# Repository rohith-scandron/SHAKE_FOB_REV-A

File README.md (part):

# SHAKE_FOB_REV-A

A PCB keychain: a shake-activated OLED "digital pet" fob. Sleeps at ~0 µA-class draw
until shaken, wakes and shows an emoji/gif on a small I2C OLED, advances to the next
one on a gentle shake, and sleeps again after 10 s idle. BLE included for a future
companion app to push new gifs. Charges and programs over USB-C. Built for JLCPCB
fab + assembly, optimized for the smallest board that still fits the parts.

## Key specs

| | |
|---|---|
| MCU | ESP32-C3FH4 (bare QFN32, 4 MB integrated flash, RISC-V, BLE 5) |
| Accelerometer | MMA8452QR1 (QFN-16 3×3 mm), transient (high-pass) wake interrupt, no polling needed. Replaced LIS2DH12TR, which is JLC "Standard PCBA only" |
| Charger | MCP73831T-2ACI/OT (SOT23-5), USB-C VBUS in, 147 mA charge rate (R_PROG = 6.8 kΩ) |
| 3V3 rail | XC6206P332MR (SOT23-3), ~1 µA Iq, 200 mA — sized for sleep-dominated duty |
| USB-C | TYPE-C-31-M-12, 16-pin, native USB D+/D− straight to the MCU (no CP2102/CH340) |
| Display | **off-board** — 0.96" 128×64 I2C OLED (SSD1306), 4 bare solder pads (GND/VCC/SCL/SDA), swappable |
| Battery | **off-board** — single-cell LiPo via 2 bare solder pads, user-sourced (the seller's cells come as bare leads, not a pre-terminated JST plug) |
| Buttons | RESET (EN→GND) and BOOT (GPIO9→GND), small SMD tactile — SuperMini-style |
| Board | 2-layer, target ≈ 25–30 × 18–22 mm, JLCPCB fab + SMT assembly |

All ICs above are on the JLCPCB parts library (LCSC part numbers in the BOM notes
below); the display and battery are intentionally *not* SMT parts — they connect
through headers/wires so either can be swapped without touching the PCB.

## BOM / JLCPCB parts library status

Checked against LCSC/JLCPCB directly (not from memory). Prices/stock are a snapshot
— reverify before ordering.

| Ref | Part | LCSC | JLCPCB library | Notes |
|---|---|---|---|---|
| U1 | ESP32-C3FH4, QFN-32-EP (5×5 mm) | C2858491 | Extended | 4233 in stock at check time |
| U4 | MMA8452QR1, QFN-16 (3×3 mm) | C11360 | Extended | Economic-PCBA OK, MSL1, 2,916 in stock. Replaced LIS2DH12TR (C110926: LGA, X-ray required → Standard PCBA only) |
| U3 | MCP73831T-2ACI/OT, SOT23-5 | C424093 | Extended (assumed) | not confirmed live, low risk either way |
| U4 | XC6206P332MR, SOT23-3 | C5446 | **Basic** | ~$0.02, ~1 µA Iq |
| U5 | USBLC6-2SC6, SOT23-6 | C7519 | Extended | USB ESD protection, use the genuine ST part |
| D2 | 1N4148WS, SOD-323 | C2128 | **Basic** | VBUS→SYS. Silicon, not Schottky, for nA reverse leakage on battery (see Power architecture) |
| Q1 | AO3401A P-MOSFET, SOT-23 | C15127 | **Basic** | BAT→SYS load-share switch (Microchip AN1149), ~14 mV drop vs ~0.3 V for a Schottky |
| R15, R16 | 1 MΩ 0402 battery-sense divider → GPIO3 | C26083 | **Basic** | + C19 100 nF; 2.1 µA |
| J1 | TYPE-C-31-M-12, USB-C 16-pin | C165948 | Extended | USB 2.0 subset only (VBUS/GND/D±/CC/SBU) |
| Y1 | 40 MHz crystal, 3225, C_L = 12 pF | **C5380316** (SOSET) | — | imported and confirmed 40 MHz on import; C13738 was mis-picked earlier (turned out to be 16 MHz) and has been removed |
| SW1, SW2 | TS342A2P tactile switch, 4×3×2 mm | C398055 | Extended | RESET + BOOT; checked for a Basic alternative, none found |
| TP1–TP4 | 4× bare solder pad (KiCad `TestPoint` lib) — OLED: GND/VCC/SCL/SDA | generic | n/a, not a real component | replaces a 2.54mm header — no connector to import, no BOM/CPL line |
| TP5–TP6 | 2× bare solder pad (KiCad `TestPoint` lib) — battery: BAT+/GND | generic | n/a, not a real component | replaces the JST-PH connector (below) — the actual battery source is bare leads, not a pre-terminated plug, so there's nothing to keep a connector for |
| ~~J3~~ | ~~S2B-PH-SM4-TB, SMD JST-PH 2-pin~~ | ~~C295747~~ | ~~Extended~~ | **dropped** — imported into the library, then superseded by TP5/TP6 once it turned out the battery isn't sold pre-terminated |
| ANT | Johanson 2450AT18A100E chip antenna | C89334 | — | in stock at check time; decided over a PCB trace, see Antenna below |
| — | RF matching, **chip-side only** (2×C 1.2–1.8pF + 1×L 2.0–3.0nH, 0201, pi network) | generic 0201 | Basic-class, commodity | antenna-side network deliberately dropped for a minimal BOM — see MCU wiring below |
| — | passives (0402/0603/0201 R/C) | generic | Basic-class, commodity | |

**11 Extended parts** after the two free swaps below (JLC BOM check,
2026-09-23): ESP32-C3FH4, MMA8452QR1, MCP73831, USBLC6-2SC6, TS342A2P,
USB-C (C165948), 40MHz crystal (C5380316), antenna (C89334), 1.5pF RF caps
(C1552), 2.2nH (C27122), 0402 LED (C71911). At $3 each that's ≈ **$33** in
loading fees. An earlier count of "5" was wrong. Free swaps with the same
footprint: 10k C25531 → **C25744** (R7–R9, R13, R14) and 100k C25530 →
**C25741** (R10), both Basic. Nothing else on the list has a Basic
equivalent in the same footprint.

**Assembly tier: Economic PCBA.** LIS2DH12TR (and its SC7A20 clone) is
flagged "Standard only" by JLC (LGA → X-ray, MSL3), so the accelerometer was
swapped to MMA8452QR1 (QFN, MSL1, Economic OK). It costs ~$1 more per part and
+3µA of sleep current, but saves ~$17 in Standard setup and the forced edge
rails.

## MCU wiring — verified against Espressif's datasheet + hardware design guidelines

Pulled `esp32-c3_datasheet_en.pdf` and the ESP32-C3 hardware design guidelines
directly (saved in [`datasheets/`](datasheets/)) rather than relying on memory.
Key points that affect the schematic:

- **Power pins**, each needs local decoupling: VDD3P3 (analog/RF, pins 2–3) — 10 µF
  + 0.1 µF (Espressif also suggests an LC filter inductor here for harmonic
  suppression — **dropped**, it's RF-certification margin rather than something
  needed for function, and the linear LDO feeding this rail is already low-noise);
  VDD3P3_RTC (pin 11) — 0.1 µF; VDD3P3_CPU (pin 17) — 0.1 µF; **VDD_SPI (pin 18)** —
  tie directly to 3V3 with a 1 µF cap, since the in-package flash on the FH4 needs
  VDD_SPI ≥ 3.0 V and this pin *cannot* be used as a GPIO on this variant. Add an ESD
  diode + ≥10 µF at the board's main power entrance too.
- **CHIP_EN**: must never float. Standard R=10 kΩ / C=1 µF RC delay to 3V3, RESET
  button pulls it to GND. Espressif's own note: on a slow/battery power rise, RC
  alone can be marginal — accepted as-is here (nearly every hobby ESP32 board ships
  with just RC), flagged as a known limitation rather than adding a supervisor IC.
- **Strapping pins** (GPIO2, GPIO8, GPIO9): GPIO9 gets an explicit pull-up
  (10 kΩ→3V3) *and* the datasheet explicitly warns not to put a capacitor on it, or
  the chip can drop into download mode — matters because BOOT button lands here.
  GPIO2 also gets a 10 kΩ pull-up ("recommended... due to glitches" even though it
  doesn't strictly gate boot mode). GPIO8 gets a 10 kΩ pull-up (R14): download boot needs GPIO8 = 1 (Table 3-3).
- **Crystal**: 40 MHz is compulsory (no internal option), ±10 ppm. Standard 2-pad
  crystal + 2 load caps. Espressif also suggests a 24 nH series inductor on the
  XTAL_P trace for harmonic suppression — **dropped**, same reasoning as the
  VDD3P3 filter above: their own guideline calls the value an "initial
  suggestion... adjust after an overall test," i.e. margin, not a requirement.
  ≥2 mm gap from the chip's clock pin, no vias on the clock trace itself, keep
  it away from the RF trace.
  **Load cap value, corrected:** the formula is `C_L = (C1×C2)/(C1+C2) + C_stray`
  (checked directly against Espressif's live HTML page — the PDF's text extraction
  had jumbled the fraction and put C_stray inside the denominator, which gave a
  wrong answer the first time around). With C1=C2=C, C_stray≈3 pF (typical PCB
  estimate), and our crystal's C_L=12 pF: `C = 2×(C_L − C_stray) = 2×(12−3) =
  18 pF`. **C1=C2=18 pF**, not the earlier 27 pF.
- **RF matching — deliberately minimal, one network not two.** Espressif's
  checklist describes two possible networks: a chip-side CLC ("must be
  placed close to the chip," no exception given) and a separate antenna-side
  CLC (which *does* have an explicit skip condition, if the antenna's
  impedance is already known to be 50Ω). The fully-by-the-book version of
  this design would have both — went there briefly, then cut back down by
  explicit request for a minimal board. **Kept the chip-side network only**
  (Espressif's generic bare-chip pi values: 1.2–1.8 pF / 2.0–3.0 nH /
  1.8–1.2 pF, 0201): a bare silicon RF pin with no matching at all is
  typically a bigger mismatch than a purpose-built antenna's nominal
  impedance drifting somewhat from board-layout differences, so this is the
  half that protects against the larger problem. **Dropped the antenna-side
  network** (Johanson's own T-network for this specific antenna, which their
  datasheet does recommend — see `docs/SCHEMATIC_BOM.md` Block 4e for the
  values, kept there for reference even though not populated). **Accepted
  trade-off, not a free simplification**: the antenna's real impedance on
  this board won't exactly match Johanson's 50Ω spec (measured on their own
  eval board), and that drift goes uncorrected — some range/efficiency traded
  for a smaller BOM, reasonable for a close-range, non-certified BLE keychain.

  Full derivation and the dropped network's values (kept for reference) in
  `docs/SCHEMATIC_BOM.md` Block 4e.
- **USB (GPIO18/19 = D−/D+)**: 22 Ω series resistors close to the chip; footprints for
  optional shunt caps and a D+ pull-up left unpopulated unless startup instability
  shows up on the bench.

### Antenna — decided: Johanson chip antenna

**Decision (confirmed with user 2026-09-22):** Johanson **2450AT18A100E** ceramic
chip antenna, LCSC C89334, in stock, ≈$0.54. The guidelines are explicit that a PCB
trace antenna needs EM simulation and real-world validation to get right — Espressif
doesn't publish a generic copy-paste trace for an arbitrary board shape, and
freehand-copying the SuperMini's antenna from a photo onto a different stackup has a
real chance of detuning it with no way for us to check. A chip antenna is a
purchasable SMD part with a vendor-validated footprint and matching network from
Johanson's own application note — a few cents of BOM for a much higher chance the
radio just works, with no lab equipment required. Still needs a copper/component
keep-out under and around it (per Johanson's app note), smaller than a full
PCB-trace keepout, so it doesn't reopen the board-size problem.

Note: the SuperMini board itself uses **ESP32-C3FN4**, which is now
**NRND (Not Recommended for New Designs)**. Good thing this board isn't cloning its
BOM — FH4 (already our pick) is the current, stocked part; "H" vs "N" also aren't
footprint-compatible, so a literal SuperMini clone wouldn't have dropped in anyway.

## Power / control architecture

```
USB-C VBUS (5V) ──┬──► MCP73831 ──► BAT ──► battery pads (TP5/TP6)
                  │                   │
                  │                   ├──► R15/R16 1M:1M ──► GPIO3 (battery sense)
                  │                   │
                  │                   └──► Q1 AO3401A (D→S) ──┐
                  │                          gate ◄── VBUS    │
                  ├──► D2 1N4148WS ─────────────────────────┴──► SYS ──► XC6206 ──► 3V3 ──► ESP32-C3, MMA8452Q, OLED
                  └──► R13 10k ──► GND (Q1 gate pull-down)
   CC1/CC2 ──5.1k──GND
   D+/D− ──────────────► MCU native USB

MMA8452Q INT1 ──► GPIO0 (RTC-capable, deep-sleep wake source, active-high)
MMA8452Q INT2 ──► GPIO1 (spare, wired for future use)
```

**Load sharing (Microchip AN1149).** USB present: Q1's gate is at VBUS, so
it's off. D2 feeds SYS and the battery charges alone, which lets the
charger terminate properly. USB absent: R13 pulls the gate low, Q1 turns
fully on, and SYS = BAT − ~14 mV. The board runs from USB with no battery
installed, and the battery never sees raw VBUS. Full reasoning and pin-out
are in [`docs/SCHEMATIC_BOM.md`](docs/SCHEMATIC_BOM.md) Block 2.

**Wake GPIO: GPIO0** (physical pin 4, `XTAL_32K_P`). ESP32-C3's RTC-IO pins — the
only ones that can wake the chip from deep sleep — are GPIO0–GPIO5 (the pins
powered by VDD3P3_RTC; datasheet §2.5, Table 2-1). Ruled out the others: GPIO2 is
a strapping pin (already has a pull-up for glitch immunity — simpler not to also
share it with an interrupt input at boot); GPIO4/GPIO5 double as JTAG (MTMS/MTDI);
GPIO0/GPIO1 are the pins for the *optional* 32.768 kHz RTC crystal, which this
board isn't populating, and the datasheet explicitly says those pins "can be used
as GPIOs" when that crystal is skipped (§1.3.5) — so GPIO0 is genuinely spare, not
a compromise. The MMA8452Q's INT pins are push-pull and always driven, so
**no pull resistor on either INT pin**. The old 100 kΩ pull-down (R10) is
deleted. It would fight the chip's power-on default (active-low, so idle
high) and waste 33 µA until firmware sets IPOL = 1.

- **Wake-on-shake is hardware, not polled.** The MMA8452Q's transient detector
  (high-pass filtered, so gravity and slow tilting are ignored) runs at 12.5 Hz in
  low-power mode (6 µA). A vigorous shake above ~1.5 g latches INT1, which wakes the
  ESP32-C3 from deep sleep. Once awake, firmware reprograms the same transient channel
  to a gentle threshold (~0.5 g at 50 Hz) for "next gif", then restores the wake
  settings before sleeping. There's only one transient channel, and it's all both
  gestures need. INT2 is wired but spare. Register values are in
  docs/SCHEMATIC_BOM.md Block 5.
- **Why a P-FET and not a second Schottky on the battery side.** The earlier
  D2+D3 diode-OR put a ~0.3V Schottky drop in the battery path. That raised
  the usable-battery floor to ~3.45V active, or ~3.6V during BLE. Q1 drops
  ~14mV, which puts the floor at **~3.1–3.2V active and ~3.3V during BLE**.
  Below that a LiPo has only a few % left, so this is effectively the whole
  cell. D2 is a **silicon** 1N4148WS on purpose: on battery it sits
  reverse-biased at ~4V, and the 1N5819WS Schottky leaks ~6–7µA there at
  25°C (read off its datasheet curve). That's over half the sleep budget.
  The 1N4148WS leaks nA. Its higher forward drop only applies on USB, where
  there's headroom to spare.
- **XC6206 (200mA) stays, with two firmware rules.** The ESP32-C3 datasheet
  only tables Wi-Fi TX current: **335mA peak @ 21dBm**, far over 200mA. So:
  **never enable Wi-Fi**, and **cap BLE TX at 0dBm**. The datasheet has no
  BLE figure, so measure the real peak at bring-up. Normal operation (CPU +
  OLED, no radio) is ~40–45mA, comfortably inside the rating. RT9013 (500mA)
  was rejected because its ~25µA Iq would roughly triple sleep current. An
  earlier "~650mV droop at 10µF, go to 47µF" derivation was withdrawn: it
  rested on an invented 50µs LDO response time. C9 = 10µF + C10 = 0.1µF is
  Espressif's reference decoupling for VDD3P3.
- **GPIO8 pull-up (R14, 10k to 3V3).** It's a strapping pin, and download
  mode needs GPIO8 = 1. In deep sleep the USB-CDC port disappears, so BOOT +
  RESET is the recovery path, and it must be reliable.
- **Battery sense (R15/R16/C19 → GPIO3).** Lets firmware stop waking the
  display below ~3.3V and show a battery icon, instead of brownout-looping
  the cell down to its protection cutoff.
- **No physical power switch.** Sleep budget, every figure sourced from the actual
  datasheet (see Battery life below, not hand-waved): **≈14.4 µA typical, board only**. Shelf
  drain from our own electronics is a non-issue at that level — LiPo self-discharge
  dominates over it. Revisit if a firmware bug (e.g. polling instead of interrupt-driven
  wake) makes this wrong.
- **No onboard battery protection IC.** Assumes the LiPo cell has its own protection
  PCB, which is standard for small hobby packs. **Confirm this once a battery is
  picked** — an unprotected cell needs a DW01+FS8205 (or similar) added.

## Battery life — 300 mAh cell

Every current figure below is from the actual component datasheet (all saved in
[`datasheets/`](datasheets/)), not estimated:

| Contributor | Typ. current | Source |
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
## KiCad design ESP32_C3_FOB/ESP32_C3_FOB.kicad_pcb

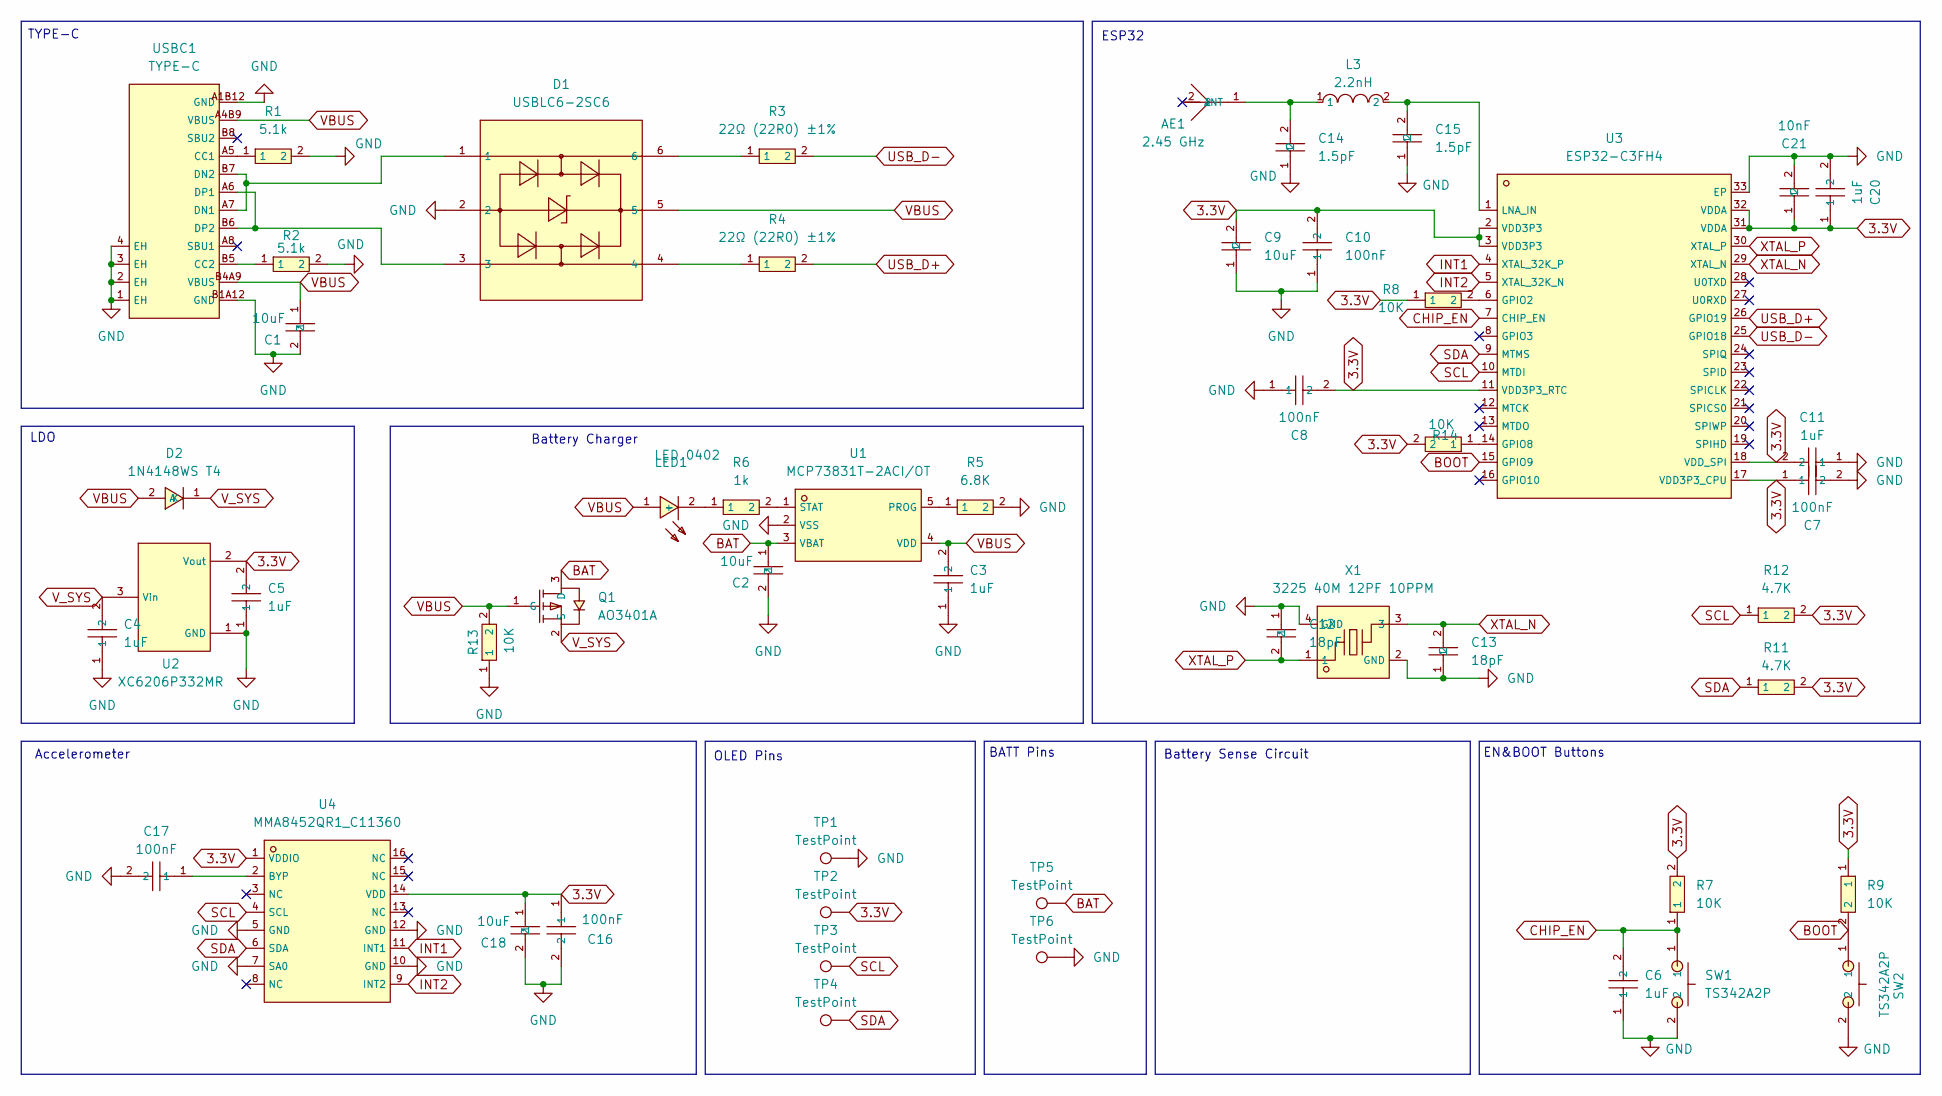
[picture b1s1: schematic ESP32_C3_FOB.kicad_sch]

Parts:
AE1: 2.45 GHz; C89334_ANT-SMD_L3_2-W1_6; LCSC C89334
C1, C2, C9, C18: 10uF; C15525_C0402; LCSC C15525
C3, C4, C5, C6, C11, C20: 1uF; C52923_C0402; LCSC C52923
C7, C8, C10, C16, C17: 100nF; C1525_C0402; LCSC C1525
C12, C13: 18pF; C1549_C0402; LCSC C1549
C14, C15: 1.5pF; C1552_C0402; LCSC C1552
C21: 10nF; C15195_C0402; LCSC C15195
D1: USBLC6-2SC6; C7519_SOT-23-6_L2_9-W1_6-P0_95-LS2_8-BL; LCSC C7519
D2: 1N4148WS T4; C2128_SOD-323_L1_8-W1_3-LS2_5-RD; LCSC C2128
L3: 2.2nH; C27122_L0402; LCSC C27122
LED1: LED 0402; C71911_LED0402-R-RD; LCSC C71911
Q1: AO3401A; C15127_SOT-23_L2_9-W1_3-P1_90-LS2_4-BR; LCSC C15127
R1, R2: 5.1k; C25905_R0402; LCSC C25905
R3, R4: 22Ω (22R0) ±1%; C25092_R0402; LCSC C25092
R5: 6.8K; C25917_R0402; LCSC C25917
R6: 1k; C11702_R0402; LCSC C11702
R7, R8, R9, R13, R14: 10K; C25744_R0402; LCSC C25744
R11, R12: 4.7K; C25900_R0402; LCSC C25900
SW1, SW2: TS342A2P; C398055_SW-SMD_L4_0-W3_0-LS5_0-EH; LCSC C398055
TP1, TP2, TP3, TP4, TP5, TP6: TestPoint; TestPoint_Pad_1.5x1.5mm
U1: MCP73831T-2ACI/OT; C424093_SOT-23-5_L3_0-W1_7-P0_95-LS2_8-BL; LCSC C424093
U2: XC6206P332MR; C5446_SOT-23-3_L2_9-W1_6-P1_90-LS2_8-BR; LCSC C5446
U3: ESP32-C3FH4; C2858491_QFN-32_L5_0-W5_0-P0_50-TL-EP3_7; LCSC C2858491
U4: MMA8452QR1_C11360; C11360_QFN-16_L3_0-W3_0-P0_50-TL_MMA8452QR1; LCSC C11360
USBC1: TYPE-C; C165948_USB-C_SMD-TYPE-C-31-M-12_1; LCSC C165948
X1: 3225 40M 12PF 10PPM; C5380316_CRYSTAL-SMD_4P-L3_2-W2_5-BL; LCSC C5380316

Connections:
3.3V: C5.2, C7.1, C8.2, C9.2, C10.2, C11.2, C16.1, C18.1, C20.1, C21.1, R7.2, R8.1, R9.1, R11.2, R12.2, R14.2, TP2.1 (1_1), U2.2 (Vout), U3.2 (VDD3P3), U3.3 (VDD3P3), U3.11 (VDD3P3_RTC), U3.17 (VDD3P3_CPU), U3.18 (VDD_SPI), U3.31 (VDDA), U3.32 (VDDA), U4.1 (VDDIO), U4.14 (VDD)
BAT: C2.1, Q1.3 (D), TP5.1 (1_1), U1.3 (VBAT)
BOOT: R9.2, SW2.1, U3.15 (GPIO9)
CHIP_EN: C6.2, R7.1, SW1.1, U3.7 (CHIP_EN)
GND: C1.2, C2.2, C3.1, C4.1, C5.1, C6.1, C7.2, C8.1, C9.1, C10.1, C11.1, C12.1, C13.1, C14.1, C15.1, C16.2, C17.2, C18.2, C20.2, C21.2, D1.2, R1.2, R2.2, R5.2, R13.1, SW1.2, SW2.2, TP1.1 (1_1), TP6.1 (1_1), U1.2 (VSS), U2.1 (GND), U3.33 (EP), U4.5 (GND), U4.7 (SA0), U4.10 (GND), U4.12 (GND), USBC1.1 (EH), USBC1.2 (EH), USBC1.3 (EH), USBC1.4 (EH), USBC1.A1B12 (GND), USBC1.B1A12 (GND), X1.2 (GND), X1.4 (GND)
INT1: U3.4 (XTAL_32K_P), U4.11 (INT1)
INT2: U3.5 (XTAL_32K_N), U4.9 (INT2)
unnamed: AE1.1 (ANT_1), C14.2, L3.1
unnamed: D1.4, R4.1
unnamed: D1.6, R3.1
unnamed: LED1.2 (-), R6.1
unnamed: R5.1, U1.5 (PROG)
unnamed: R6.2, U1.1 (STAT)
unnamed: R8.2, U3.6 (GPIO2)
unnamed: R14.1, U3.14 (GPIO8)
unnamed: C15.2, L3.2, U3.1 (LNA_IN)
unnamed: C17.1, U4.2 (BYP)
unnamed: R1.1, USBC1.A5 (CC1)
unnamed: R2.1, USBC1.B5 (CC2)
unnamed: D1.1, USBC1.A7 (DN1), USBC1.B7 (DN2)
unnamed: D1.3, USBC1.A6 (DP1), USBC1.B6 (DP2)
SCL: R12.1, TP3.1 (1_1), U3.10 (MTDI), U4.4 (SCL)
SDA: R11.1, TP4.1 (1_1), U3.9 (MTMS), U4.6 (SDA)
USB_D+: R4.2, U3.26 (GPIO19)
USB_D-: R3.2, U3.25 (GPIO18)
VBUS: C1.1, C3.2, D1.5, D2.2 (A), LED1.1 (+), Q1.1 (G), R13.2, U1.4 (VDD), USBC1.A4B9 (VBUS), USBC1.B4A9 (VBUS)
V_SYS: C4.2, D2.1 (K), Q1.2 (S), U2.3 (Vin)
XTAL_N: C13.2, U3.29 (XTAL_N), X1.3
XTAL_P: C12.2, U3.30 (XTAL_P), X1.1

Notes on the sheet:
LDO
Accelerometer
TYPE-C
EN&BOOT Buttons
ESP32
BATT Pins
OLED Pins
Battery Sense Circuit
Battery Charger

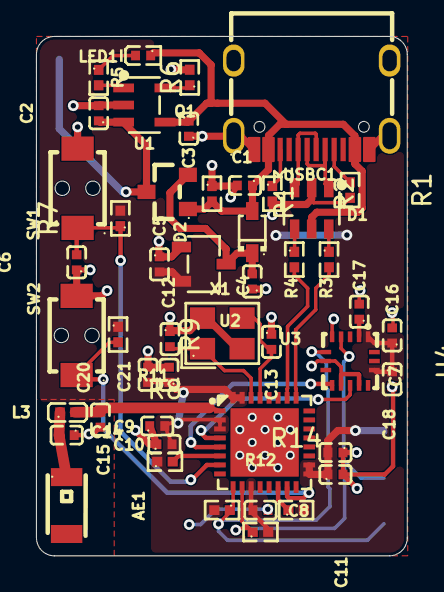
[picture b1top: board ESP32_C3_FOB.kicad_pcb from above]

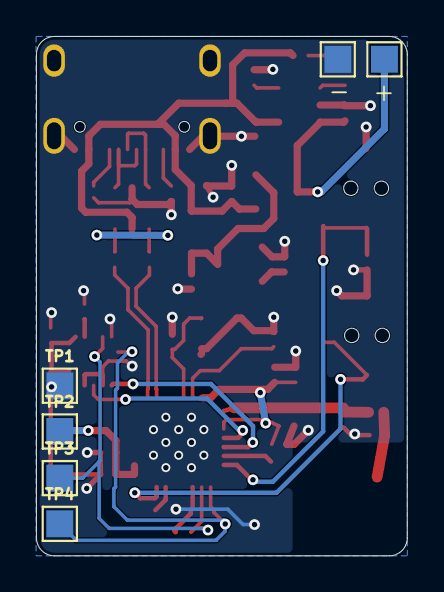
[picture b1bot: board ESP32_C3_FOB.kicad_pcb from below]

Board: 2 copper layers, 20.6 x 28.9 mm, 53 parts (6 on the bottom side), 29 nets.
